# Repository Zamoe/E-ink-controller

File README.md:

# E-ink-controller

This project uses an e-ink display, buttons and a rotary encoder to create a dymanic smart-home controller. The board connects to WiFi and uses MQTT to connect to a HomeAssistant instance. The E-ink display shows devices being controlled and their current status and the buttons and encoder are used to control the devices. 

## Hardware 

ESP32 DevKit-v1 as the system MCU.
Display is the waveshare 2.13" E-ink Display.
Rotary Knob is the DF Robot Encoder. 
WS2812 Addressable RGB Led Strip.
8 standard buttons are connected to one GPIO pin, using an analog button array configuration. 

See the schematic file for the wiring diagram:

## Software
The code is constructed using the Arduino IDE with various libraries used for the screen, encoder and buttons. 

## Casing

The 3D print files for the casing can be found in the stl file.

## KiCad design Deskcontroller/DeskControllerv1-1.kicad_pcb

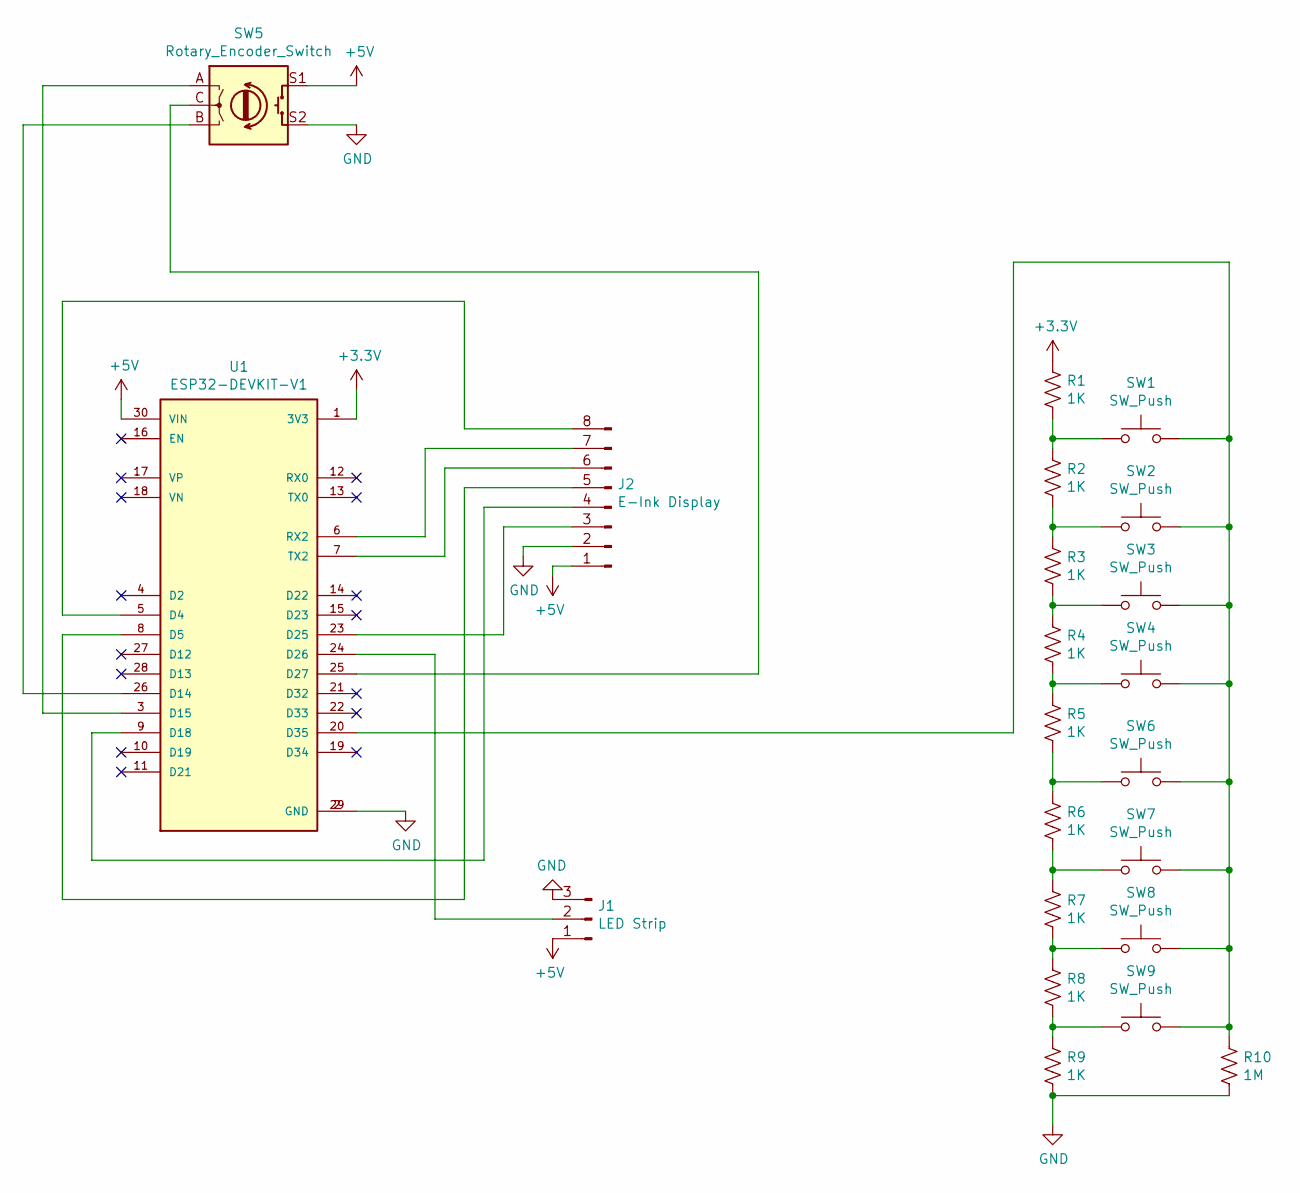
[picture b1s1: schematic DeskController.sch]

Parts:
J1: LED Strip; JST_GH_BM03B-GHS-TBT_1x03-1MP_P1.25mm_Vertical
J2: E-Ink Display; PinHeader_1x08_P1.27mm_Vertical
R1, R2, R3, R4, R5, R6, R7, R8, R9: 1K; R_Axial_DIN0204_L3.6mm_D1.6mm_P5.08mm_Horizontal
R10: 1M; R_Axial_DIN0204_L3.6mm_D1.6mm_P5.08mm_Horizontal
SW1, SW2, SW3, SW4, SW6, SW7, SW8, SW9: SW_Push; SW_Cherry_MX_1.00u_Plate
SW5: Rotary_Encoder_Switch; RotaryEncoder_Alps_EC11E-Switch_Vertical_H20mm_CircularMoun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
U1: ESP32-DEVKIT-V1; MODULE_ESP32_DEVKIT_V1; PARTREV N/A

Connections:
+3V3: R1.1, U1.1 (3V3)
+5V: J1.1, J2.1, SW5.S1, U1.30 (VIN)
GND: J1.3, J2.2, R9.2, R10.2, SW5.S2, U1.2 (GND), U1.29 (GND)
unnamed: J1.2, U1.24 (D26)
unnamed: J2.3, U1.23 (D25)
unnamed: J2.4, U1.9 (D18)
unnamed: J2.5, U1.8 (D5)
unnamed: J2.6, U1.7 (TX2)
unnamed: J2.7, U1.6 (RX2)
unnamed: J2.8, U1.5 (D4)
unnamed: R1.2, R2.1, SW1.1
unnamed: R2.2, R3.1, SW2.1
unnamed: R3.2, R4.1, SW3.1
unnamed: R4.2, R5.1, SW4.1
unnamed: R5.2, R6.1, SW6.1
unnamed: R6.2, R7.1, SW7.1
unnamed: R7.2, R8.1, SW8.1
unnamed: R8.2, R9.1, SW9.1
unnamed: R10.1, SW1.2, SW2.2, SW3.2, SW4.2, SW6.2, SW7.2, SW8.2, SW9.2, U1.20 (D35)
unnamed: SW5.A, U1.3 (D15)
unnamed: SW5.B, U1.26 (D14)
unnamed: SW5.C, U1.25 (D27)

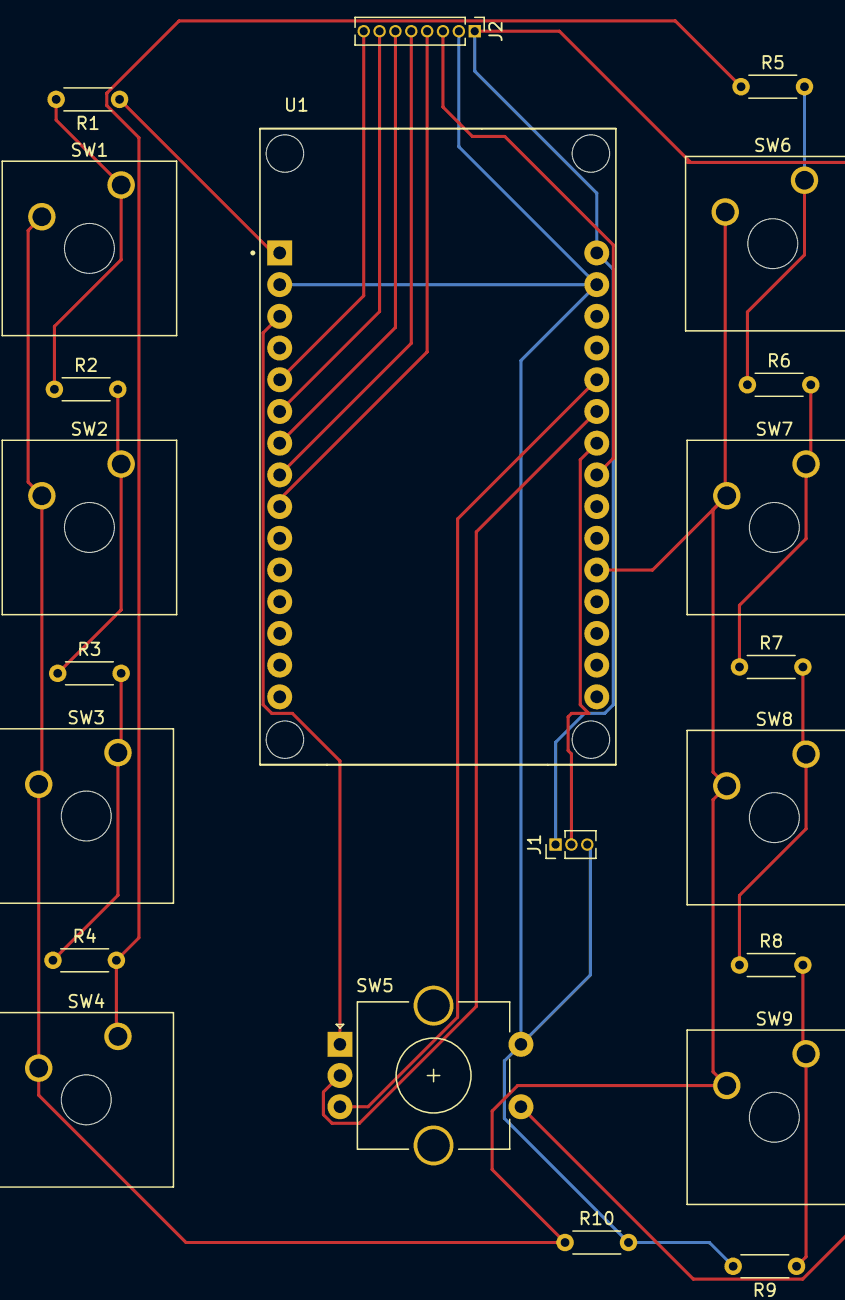
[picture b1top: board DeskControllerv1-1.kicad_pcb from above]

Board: 2 copper layers, 22 parts (0 on the bottom side), 22 nets.

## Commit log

2024-04-23 Reupload to new git page
    V3.4:
    - LEDs working
    - Rotary working
    - Error in button array
    - Display working
2024-04-23 Kicad files for PCB design
